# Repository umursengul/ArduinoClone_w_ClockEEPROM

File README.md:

# ArduinoClone_w_ClockEEPROM
A battery powered Arduino clone with integrated RTC and EEPROM.

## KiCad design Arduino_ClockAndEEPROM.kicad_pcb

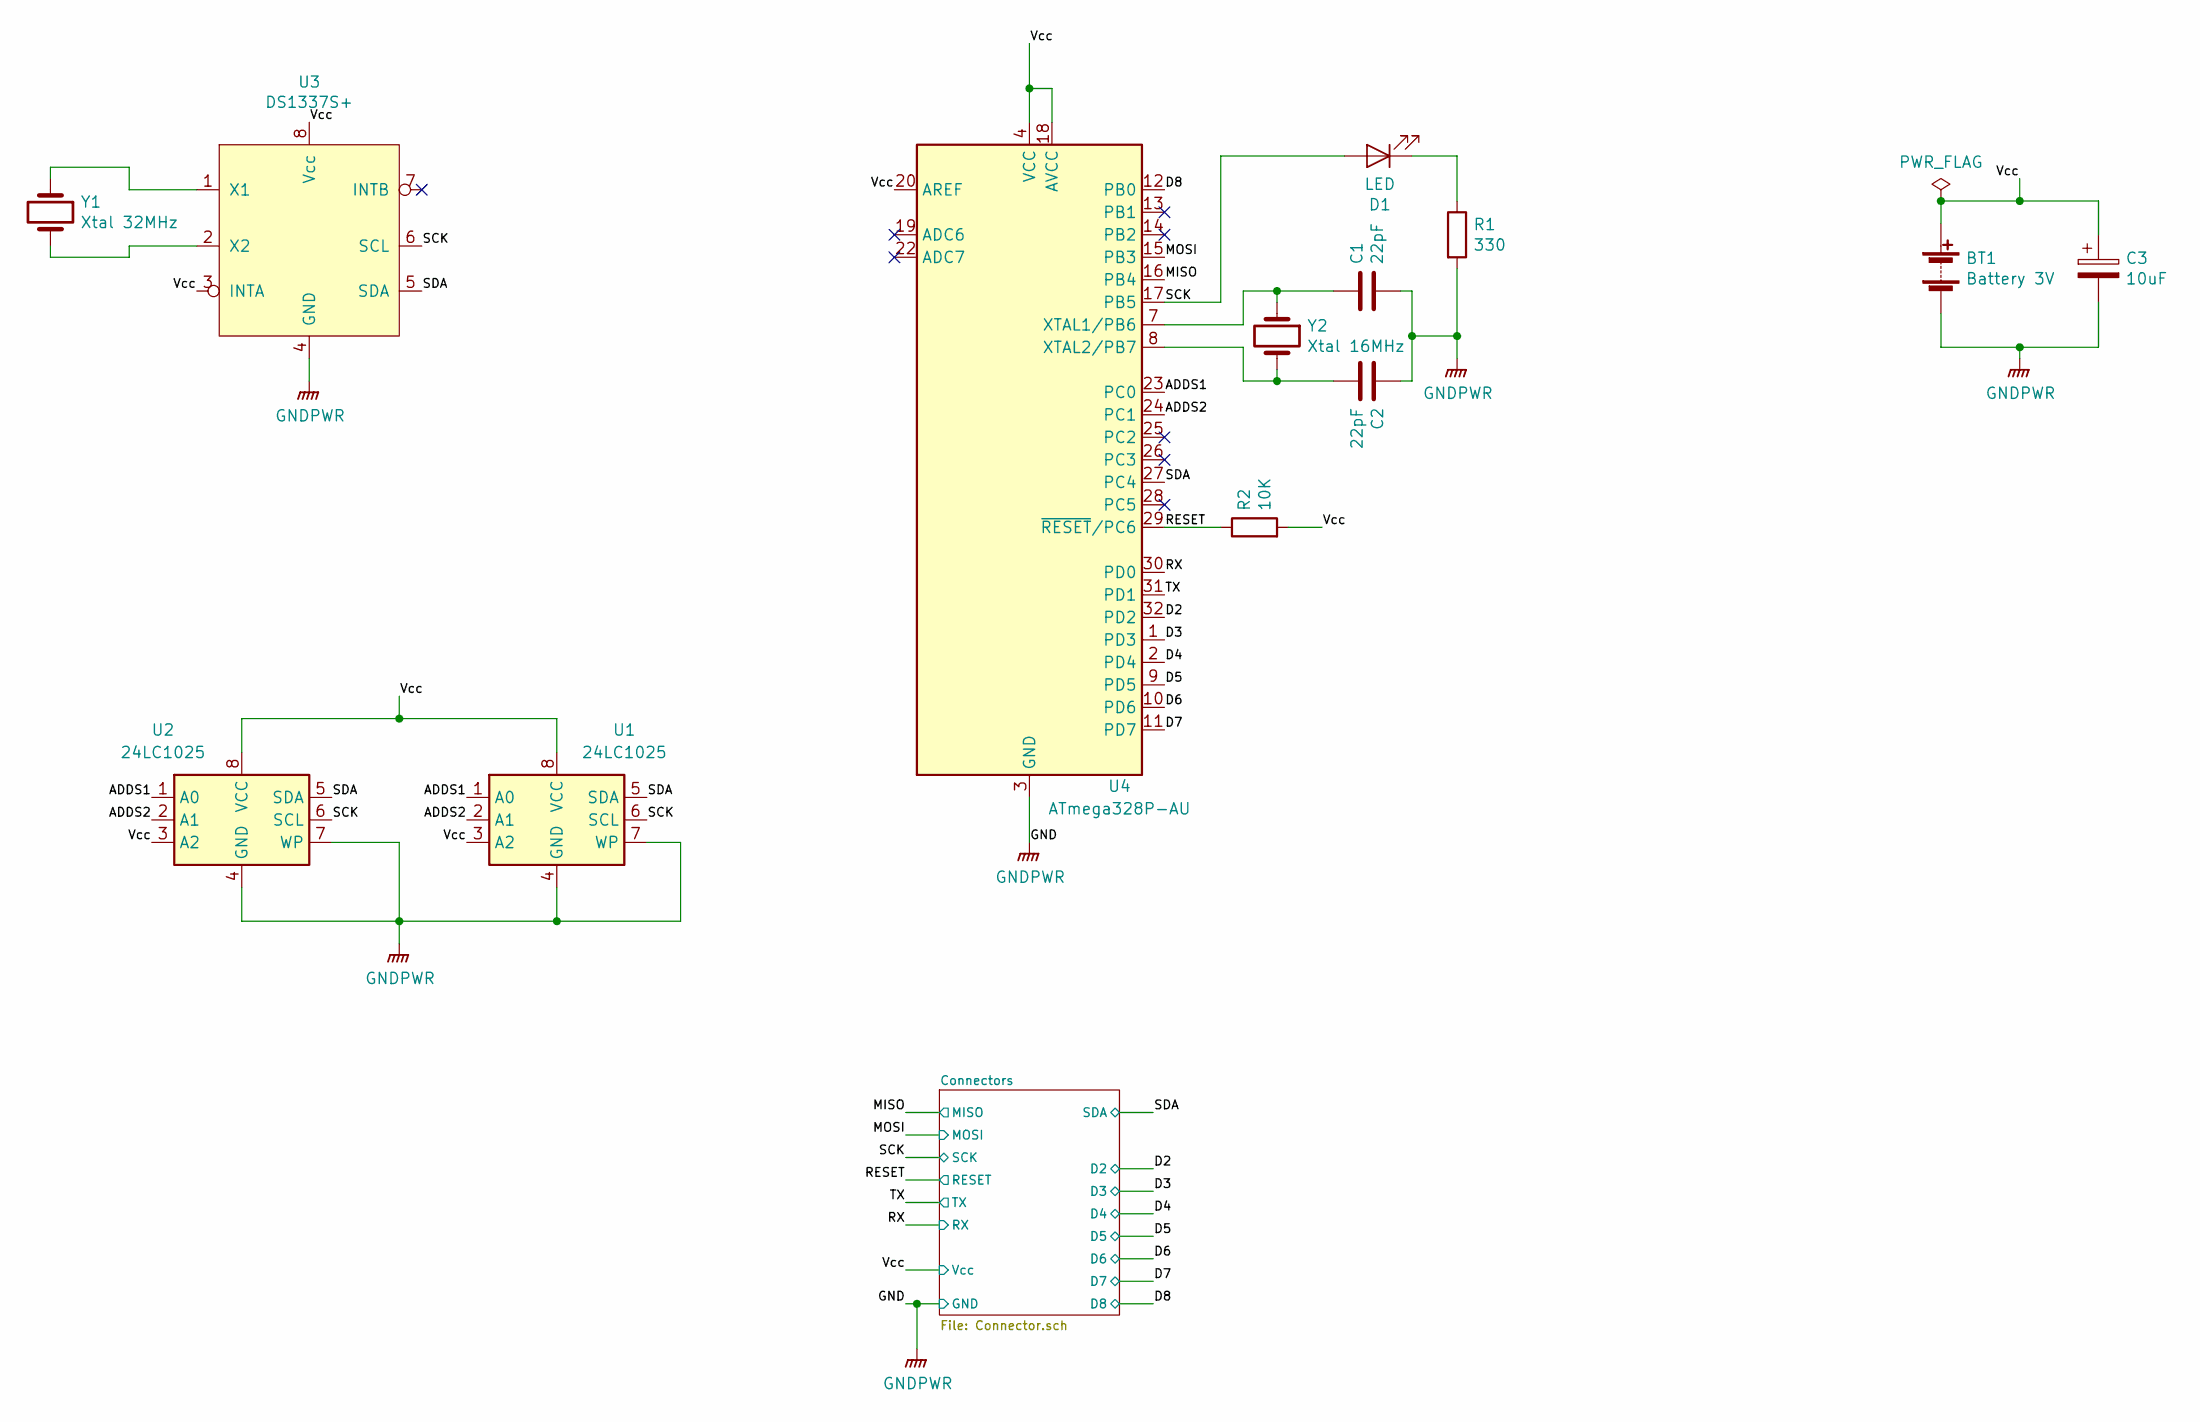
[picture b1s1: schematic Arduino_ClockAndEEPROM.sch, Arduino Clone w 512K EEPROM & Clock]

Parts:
BT1: Battery 3V; PinHeader_1x02_P2.54mm_Vertical
C1, C2: 22pF; C_0805_2012Metric_Pad1.15x1.40mm_HandSolder
C3: 10uF; C_0805_2012Metric_Pad1.15x1.40mm_HandSolder
D1: LED; LED_0805_2012Metric_Pad1.15x1.40mm_HandSolder
R1: 330; R_0815_2038Metric_Pad1.53x4.00mm_HandSolder
R2: 10K; R_0815_2038Metric_Pad1.53x4.00mm_HandSolder
U1, U2: 24LC1025; SOIJ-8_5.3x5.3mm_P1.27mm
U3: DS1337S+; SO-8_5.3x6.2mm_P1.27mm
U4: ATmega328P-AU; TQFP-32_7x7mm_P0.8mm
Y1: Xtal 32MHz; Crystal_SMD_MicroCrystal_CC7V-T1A-2Pin_3.2x1.5mm
Y2: Xtal 16MHz; Crystal_SMD_5032-2Pin_5.0x3.2mm_HandSoldering

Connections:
/ADDS1: U1.1 (A0), U2.1 (A0), U4.23 (PC0)
/ADDS2: U1.2 (A1), U2.2 (A1), U4.24 (PC1)
/D2: U4.32 (PD2); also elsewhere on the board
/D3: U4.1 (PD3); also elsewhere on the board
/D4: U4.2 (PD4); also elsewhere on the board
/D5: U4.9 (PD5); also elsewhere on the board
/D6: U4.10 (PD6); also elsewhere on the board
/D7: U4.11 (PD7); also elsewhere on the board
/D8: U4.12 (PB0); also elsewhere on the board
/MISO: U4.16 (PB4); also elsewhere on the board
/MOSI: U4.15 (PB3); also elsewhere on the board
/RESET: R2.1, U4.29 (~RESET~/PC6); also elsewhere on the board
/RX: U4.30 (PD0); also elsewhere on the board
/SCK: D1.2 (A), U1.6 (SCL), U2.6 (SCL), U3.6 (SCL), U4.17 (PB5); also elsewhere on the board
/SDA: U1.5 (SDA), U2.5 (SDA), U3.5 (SDA), U4.27 (PC4); also elsewhere on the board
/TX: U4.31 (PD1); also elsewhere on the board
/Vcc: BT1.1 (+), C3.1, R2.2, U1.3 (A2), U1.8 (VCC), U2.3 (A2), U2.8 (VCC), U3.3 (INTA), U3.8 (Vcc), U4.4 (VCC), U4.6 (VCC), U4.18 (AVCC), U4.20 (AREF); also elsewhere on the board
GNDPWR: BT1.2 (-), C1.2, C2.1, C3.2, R1.2, U1.4 (GND), U1.7 (WP), U2.4 (GND), U2.7 (WP), U3.4 (GND), U4.3 (GND), U4.5 (GND), U4.21 (GND); also elsewhere on the board
unnamed: C1.1, U4.7 (XTAL1/PB6), Y2.1
unnamed: C2.2, U4.8 (XTAL2/PB7), Y2.2
unnamed: D1.1 (K), R1.1
unnamed: U3.1 (X1), Y1.1
unnamed: U3.2 (X2), Y1.2

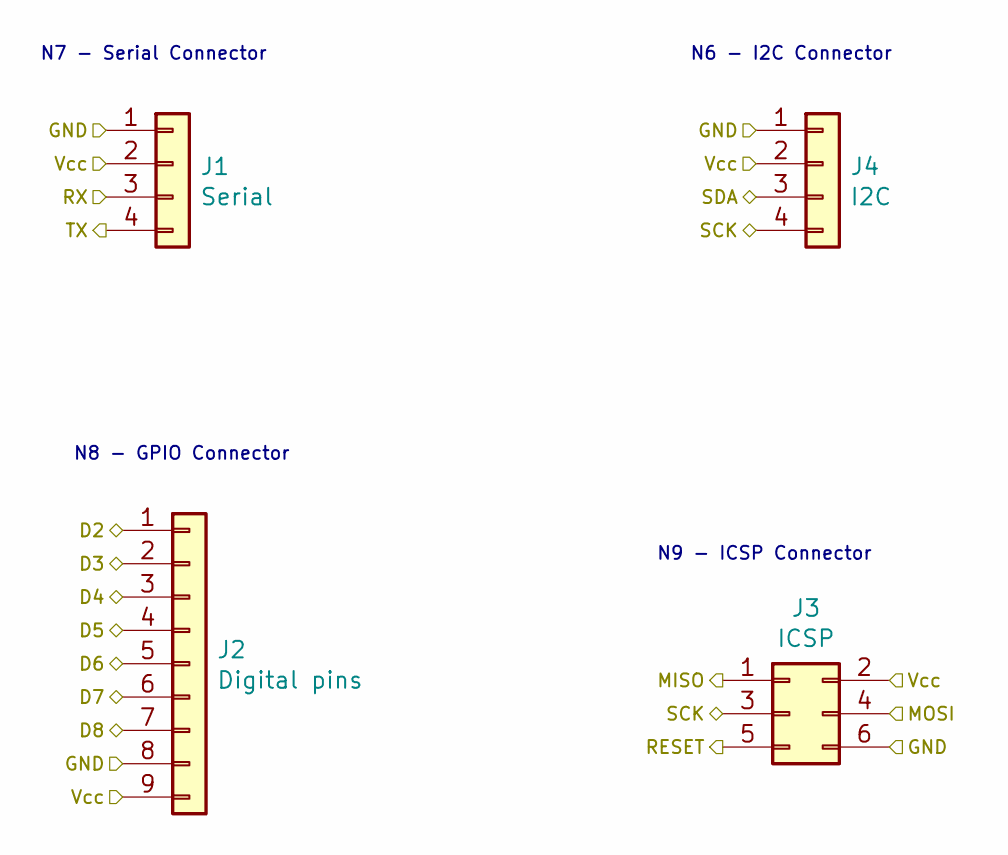
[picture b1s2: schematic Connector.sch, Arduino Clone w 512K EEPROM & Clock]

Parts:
J1: Serial; PinHeader_1x04_P2.54mm_Vertical
J2: Digital pins; PinHeader_1x09_P2.54mm_Vertical
J3: ICSP; PinSocket_2x03_P2.54mm_Vertical
J4: I2C; PinSocket_1x04_P2.54mm_Vertical

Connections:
/D2: J2.1; also elsewhere on the board
/D3: J2.2; also elsewhere on the board
/D4: J2.3; also elsewhere on the board
/D5: J2.4; also elsewhere on the board
/D6: J2.5; also elsewhere on the board
/D7: J2.6; also elsewhere on the board
/D8: J2.7; also elsewhere on the board
/MISO: J3.1; also elsewhere on the board
/MOSI: J3.4; also elsewhere on the board
/RESET: J3.5; also elsewhere on the board
/RX: J1.3; also elsewhere on the board
/SCK: J3.3, J4.4; also elsewhere on the board
/SDA: J4.3; also elsewhere on the board
/TX: J1.4; also elsewhere on the board
/Vcc: J1.2, J2.9, J3.2, J4.2; also elsewhere on the board
GNDPWR: J1.1, J2.8, J3.6, J4.1; also elsewhere on the board

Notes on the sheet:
N6 - I2C Connector
N7 - Serial Connector
N8 - GPIO Connector
N9 - ICSP Connector

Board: 4 copper layers, 17 parts (0 on the bottom side), 23 nets, no tracks yet.

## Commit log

2019-06-06 First commit.
2019-06-06 Setup the title block in schematic sheet.
2019-06-06 Create LICENSE
2019-06-06 Created new child sheet, added majority of the symbols.
2019-06-06 Added rest of the symbols.
2019-06-06 Added missing symbols, arranged symbols, annotated.
2019-06-06 Completed associations and added component values.
2019-06-06 Completed wiring in the connectors sheet.
2019-06-06 Completed wiring in all sheets.
2019-06-06 Added functional block descriptions.
2019-06-06 Created netlist file.
2019-06-06 Started work in Pcbnew.
2019-06-06 Set design rules.
2019-06-06 Layout complete.
2019-06-06 Layout finalized and mounting holes are added.
2019-06-06 Fully routed board in 2 layers.
2019-06-06 Silkscreen and graphics added, PCB layout finalized.
